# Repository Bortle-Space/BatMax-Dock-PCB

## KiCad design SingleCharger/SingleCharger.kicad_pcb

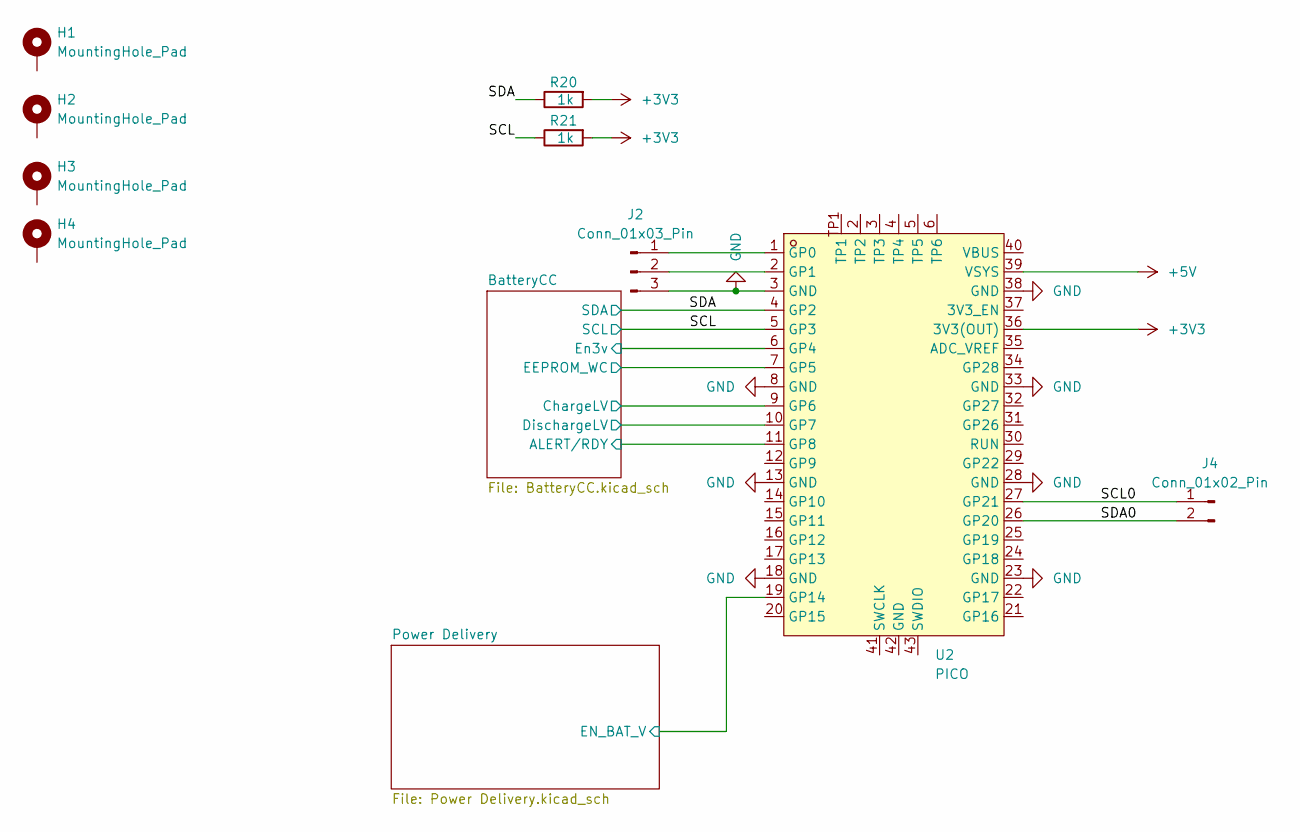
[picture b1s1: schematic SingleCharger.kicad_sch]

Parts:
H1, H2, H3, H4: MountingHole_Pad; MountingHole_3.2mm_M3_DIN965_Pad_TopBottom
J2: Conn_01x03_Pin; PinHeader_1x03_P2.54mm_Vertical
J4: Conn_01x02_Pin; PinHeader_1x02_P2.54mm_Vertical
R20, R21: 1k; R_1206_3216Metric_Pad1.30x1.75mm_HandSolder
U2: PICO; RaspberryPi_Pico_Common_THT; LCSC Part C7203002

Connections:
+3V3: R20.2, R21.2, U2.36 (3V3(OUT)); also elsewhere on the board
+5V: U2.39 (VSYS); also elsewhere on the board
/BatteryCC/ALERT/RDY: U2.11 (GP8); also elsewhere on the board
/BatteryCC/Battery/EEPROM_WC: U2.7 (GP5); also elsewhere on the board
/BatteryCC/ChargeLV: U2.9 (GP6); also elsewhere on the board
/DischargeLV: U2.10 (GP7)
/En3v: U2.6 (GP4)
/Power Delivery/EN_BAT_V: U2.19 (GP14); also elsewhere on the board
/SCL: R21.1, U2.5 (GP3); also elsewhere on the board
/SCL0: J4.1, U2.27 (GP21)
/SDA: R20.1, U2.4 (GP2); also elsewhere on the board
/SDA0: J4.2, U2.26 (GP20)
GND: J2.3, U2.3 (GND), U2.8 (GND), U2.13 (GND), U2.18 (GND), U2.23 (GND), U2.28 (GND), U2.33 (GND), U2.38 (GND); also elsewhere on the board
unnamed: J2.1, U2.1 (GP0)
unnamed: J2.2, U2.2 (GP1)

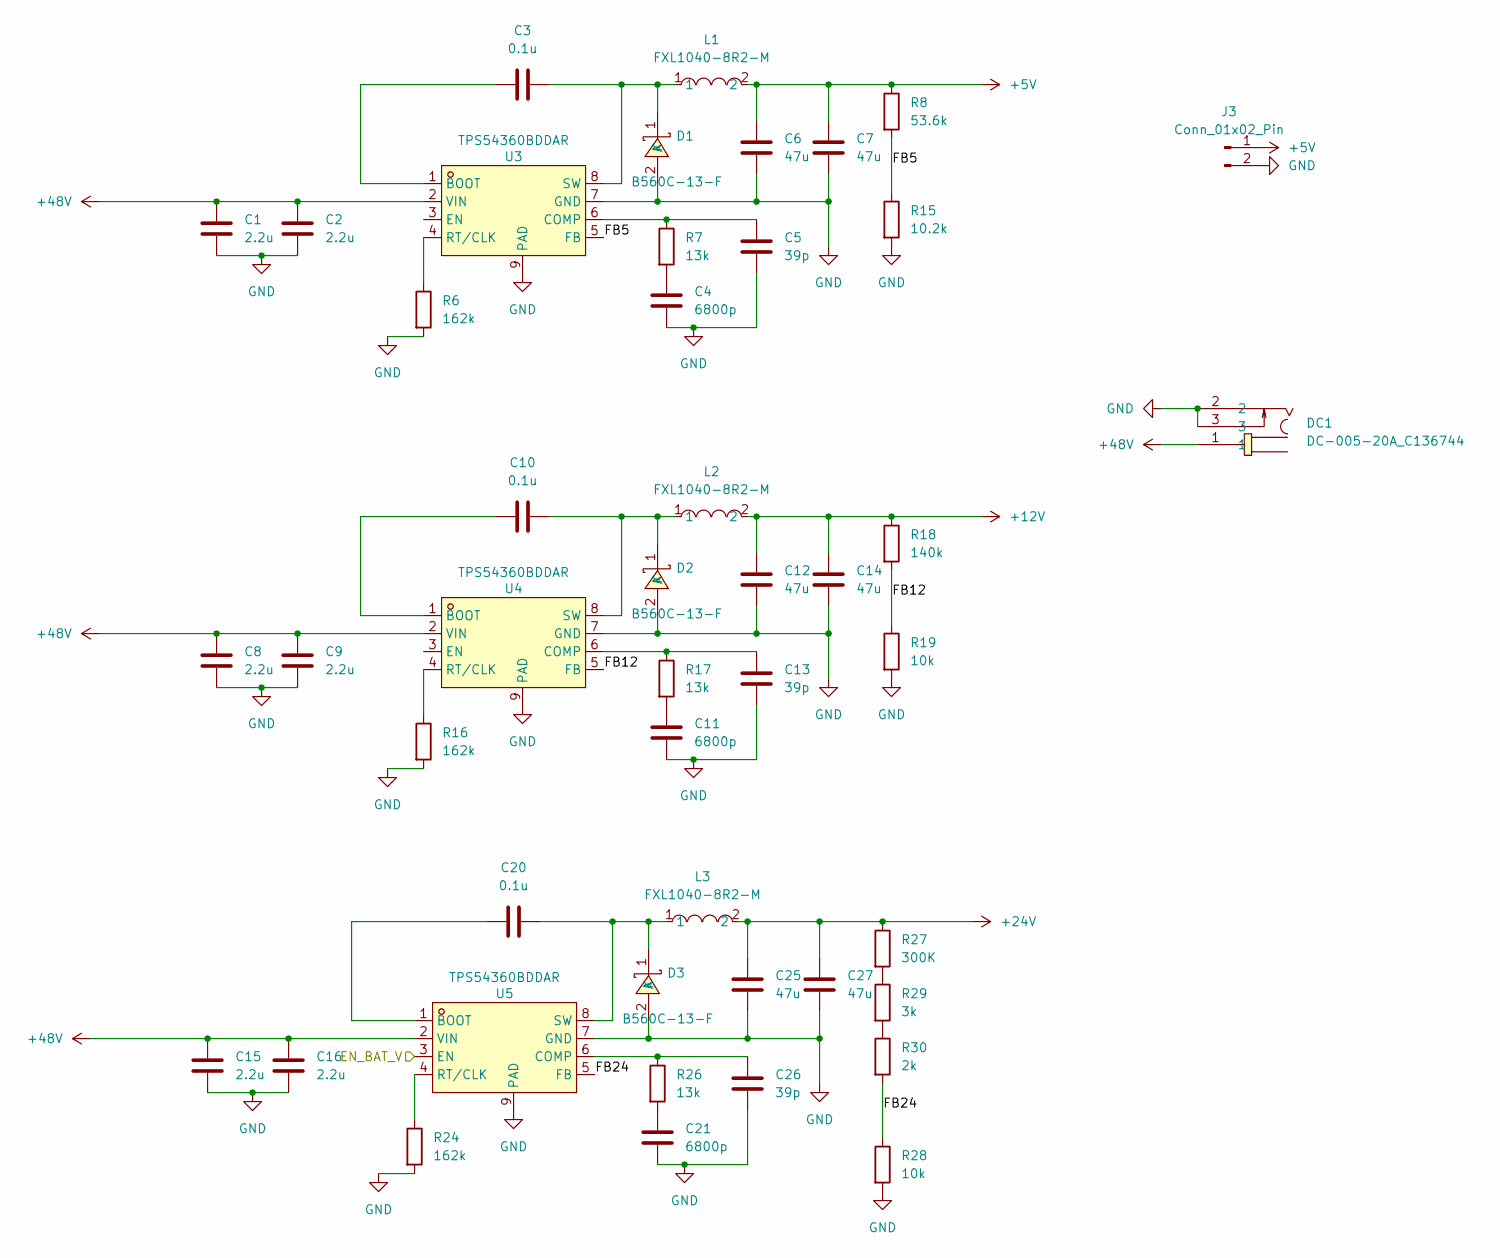
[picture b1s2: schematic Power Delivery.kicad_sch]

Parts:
C1, C2, C8, C9, C15, C16: 2.2u; C_1206_3216Metric; LCSC Part C170101
C3, C10, C20: 0.1u; C_1206_3216Metric; LCSC Part C56392
C4, C11, C21: 6800p; C_1206_3216Metric; LCSC Part C2760541
C5, C13, C26: 39p; C_1206_3216Metric; LCSC Part C5186878
C6, C7, C12, C14, C25, C27: 47u; C_1206_3216Metric; LCSC Part C94034
D1, D2, D3: B560C-13-F; SMC_L7.1-W6.2-LS8.1-RD; LCSC Part C85100
DC1: DC-005-20A_C136744; DC-IN-TH_DC-005-20A; LCSC Part C136744
J3: Conn_01x02_Pin; PinHeader_1x02_P2.54mm_Vertical
L1, L2, L3: FXL1040-8R2-M; IND-SMD_L11.5-W10.0_FXL1040; LCSC Part C167232
R6, R16, R24: 162k; R_1206_3216Metric_Pad1.30x1.75mm_HandSolder; LCSC Part C22815
R7, R17, R26: 13k; R_1206_3216Metric_Pad1.30x1.75mm_HandSolder; LCSC Part C445658
R8: 53.6k; R_1206_3216Metric_Pad1.30x1.75mm_HandSolder; LCSC Part C21398
R15: 10.2k; R_1206_3216Metric_Pad1.30x1.75mm_HandSolder; LCSC Part C21398
R18: 140k; R_1206_3216Metric_Pad1.30x1.75mm_HandSolder; LCSC Part C21398
R19, R28: 10k; R_1206_3216Metric_Pad1.30x1.75mm_HandSolder; LCSC Part C21398
R27: 300K; R_1206_3216Metric_Pad1.30x1.75mm_HandSolder; LCSC Part C21398
R29: 3k; R_1206_3216Metric_Pad1.30x1.75mm_HandSolder; LCSC Part C21398
R30: 2k; R_1206_3216Metric_Pad1.30x1.75mm_HandSolder; LCSC Part C21398
U3, U4, U5: TPS54360BDDAR; SOIC-8_L5.0-W4.0-P1.27-LS6.0-BL-EP2.0; LCSC Part C524806

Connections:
+5V: C6.1, C7.1, J3.1, L1.2, R8.1; also elsewhere on the board
+12V: C12.1, C14.1, L2.2, R18.1; also elsewhere on the board
+24V: C25.1, C27.1, L3.2, R27.1; also elsewhere on the board
+48V: C1.1, C2.1, C8.1, C9.1, C15.1, C16.1, DC1.1, U3.2 (VIN), U4.2 (VIN), U5.2 (VIN)
/Power Delivery/EN_BAT_V: U5.3 (EN); also elsewhere on the board
/Power Delivery/FB5: R8.2, R15.1, U3.5 (FB)
/Power Delivery/FB12: R18.2, R19.1, U4.5 (FB)
/Power Delivery/FB24: R28.1, R30.2, U5.5 (FB)
GND: C1.2, C2.2, C4.2, C5.2, C6.2, C7.2, C8.2, C9.2, C11.2, C12.2, C13.2, C14.2, C15.2, C16.2, C21.2, C25.2, C26.2, C27.2, D1.2 (A), D2.2 (A), D3.2 (A), DC1.2, DC1.3, J3.2, R6.2, R15.2, R16.2, R19.2, R24.2, R28.2, U3.7 (GND), U3.9 (PAD), U4.7 (GND), U4.9 (PAD), U5.7 (GND), U5.9 (PAD); also elsewhere on the board
unnamed: C4.1, R7.2
unnamed: C11.1, R17.2
unnamed: C21.1, R26.2
unnamed: C3.2, D1.1 (K), L1.1, U3.8 (SW)
unnamed: C10.2, D2.1 (K), L2.1, U4.8 (SW)
unnamed: C20.2, D3.1 (K), L3.1, U5.8 (SW)
unnamed: R27.2, R29.1
unnamed: R29.2, R30.1
unnamed: C3.1, U3.1 (BOOT)
unnamed: C5.1, R7.1, U3.6 (COMP)
unnamed: R6.1, U3.4 (RT/CLK)
unnamed: C10.1, U4.1 (BOOT)
unnamed: C13.1, R17.1, U4.6 (COMP)
unnamed: R16.1, U4.4 (RT/CLK)
unnamed: C20.1, U5.1 (BOOT)
unnamed: C26.1, R26.1, U5.6 (COMP)
unnamed: R24.1, U5.4 (RT/CLK)

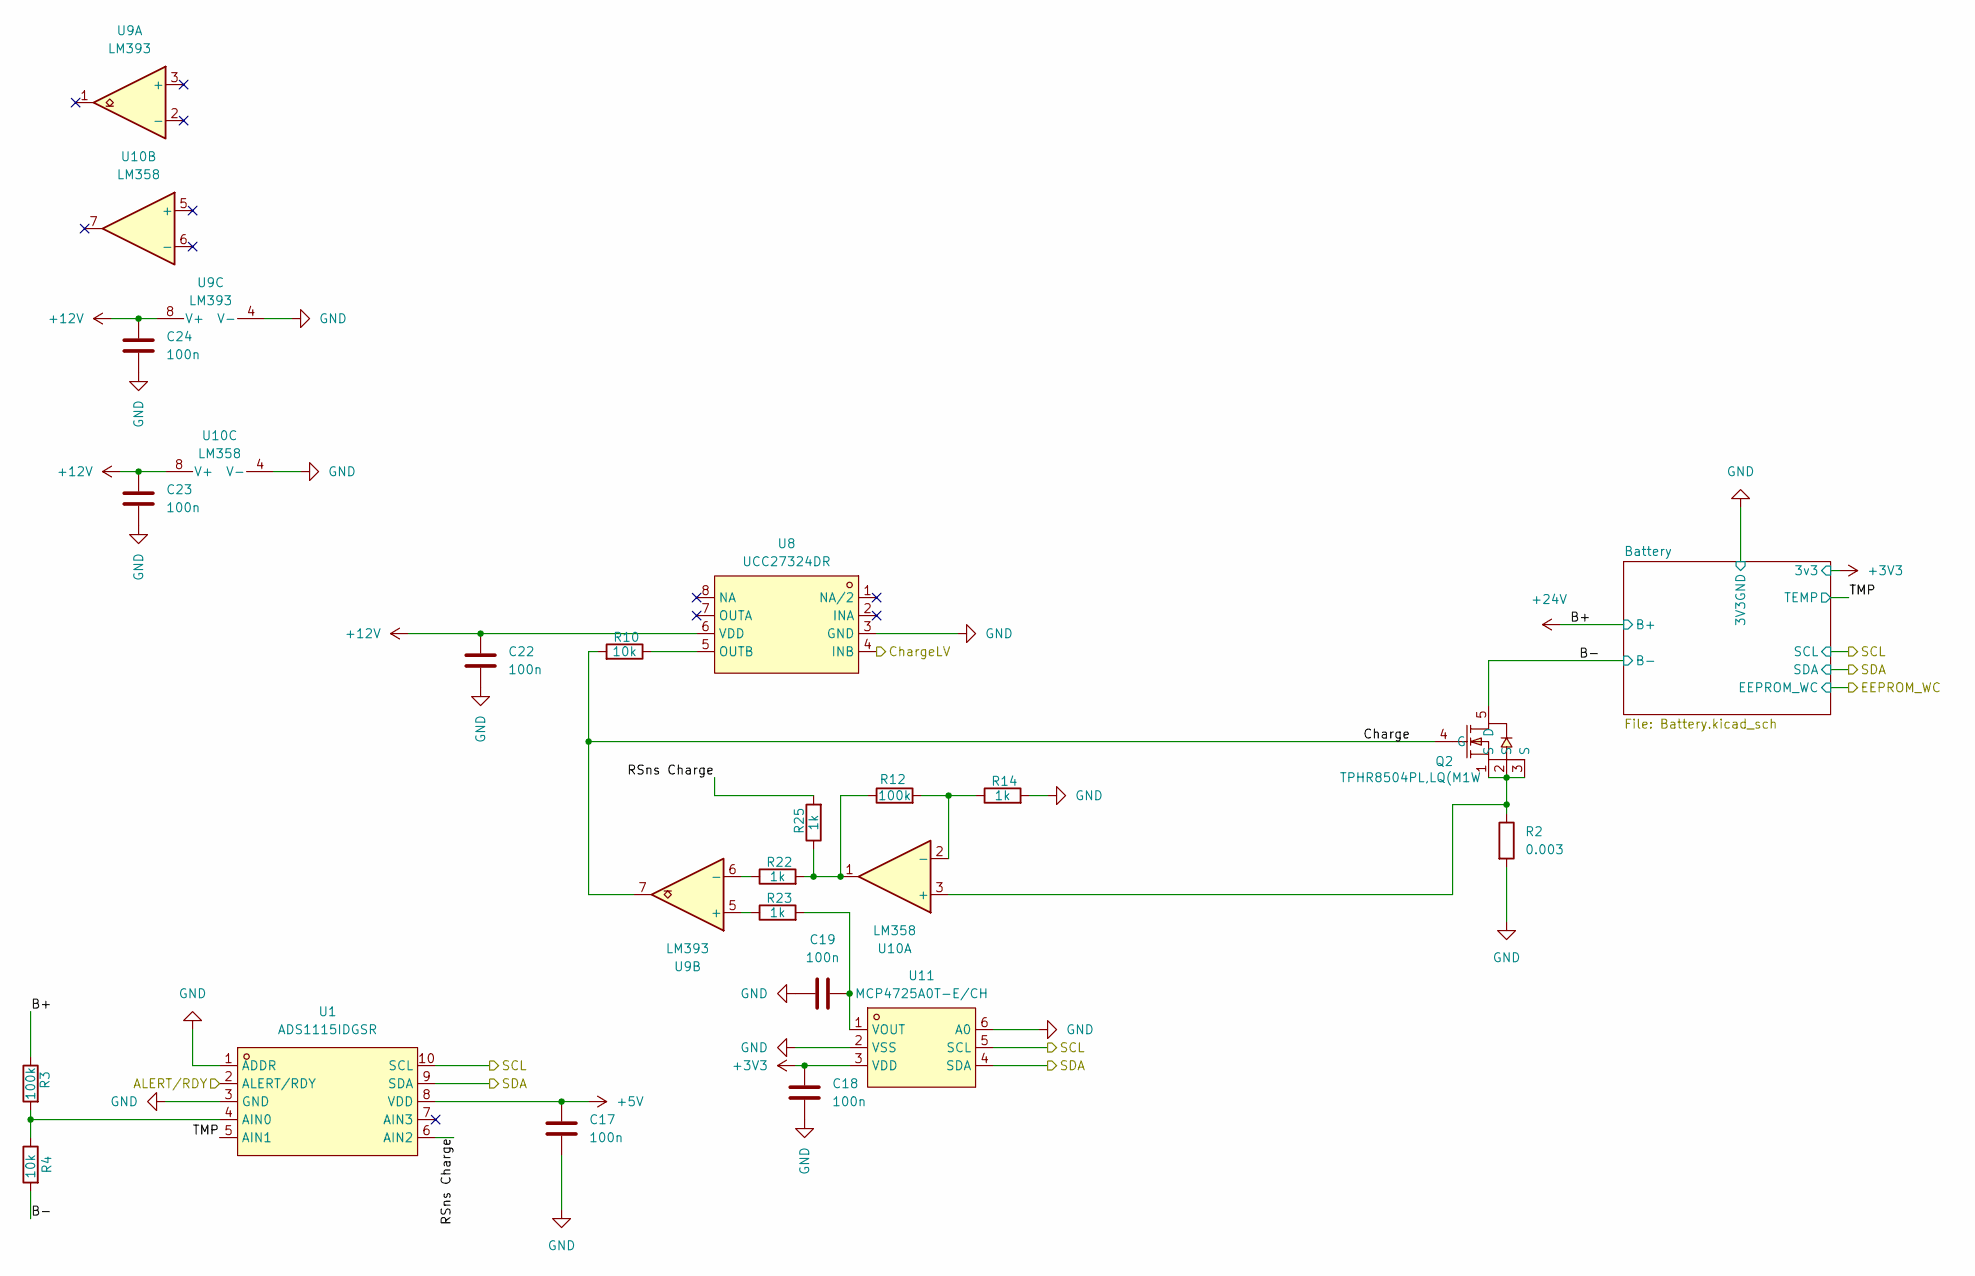
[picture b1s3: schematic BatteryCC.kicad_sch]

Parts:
C17, C18, C19, C22, C23, C24: 100n; R_1206_3216Metric_Pad1.30x1.75mm_HandSolder
Q2: TPHR8504PL,LQ(M1W; DFN-5_L4.9-W5.9-P1.27-LS6.2-BL; LCSC Part C22388172
R2: 0.003; R_1206_3216Metric_Pad1.30x1.75mm_HandSolder
R3, R12: 100k; R_1206_3216Metric_Pad1.30x1.75mm_HandSolder
R4, R10: 10k; R_1206_3216Metric_Pad1.30x1.75mm_HandSolder
R14, R22, R23, R25: 1k; R_1206_3216Metric_Pad1.30x1.75mm_HandSolder
U1: ADS1115IDGSR; MSOP-10_L3.0-W3.0-P0.50-LS5.0-BL; LCSC Part C37593
U8: UCC27324DR; SOIC-8_L5.0-W4.0-P1.27-LS6.0-BL; LCSC Part C46427
U9: LM393; SOP-8_L4.9-W3.9-P1.27-LS6.0-BL
U10: LM358; SOP-8_L4.9-W3.9-P1.27-LS6.0-BL
U11: MCP4725A0T-E/CH; SOT-23-6_L2.9-W1.6-P0.95-LS2.8-BL; LCSC Part C144198

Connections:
+3V3: C18.1, U11.3 (VDD); also elsewhere on the board
+5V: C17.1, U1.8 (VDD); also elsewhere on the board
+12V: C22.1, C23.1, C24.1, U8.6 (VDD), U9.8 (V+), U10.8 (V+); also elsewhere on the board
+24V: R3.1; also elsewhere on the board
/BatteryCC/ALERT/RDY: U1.2 (ALERT/RDY); also elsewhere on the board
/BatteryCC/B-: Q2.5 (D), R4.2; also elsewhere on the board
/BatteryCC/Charge: Q2.4 (G), R10.2, U9.7
/BatteryCC/ChargeLV: U8.4 (INB); also elsewhere on the board
/BatteryCC/RSns Charge: R25.2, U1.6 (AIN2)
/BatteryCC/TMP: U1.5 (AIN1); also elsewhere on the board
/SCL: U1.10 (SCL), U11.5 (SCL); also elsewhere on the board
/SDA: U1.9 (SDA), U11.4 (SDA); also elsewhere on the board
GND: C17.2, C18.2, C19.1, C22.2, C23.2, C24.2, R2.2, R14.2, U1.1 (ADDR), U1.3 (GND), U8.3 (GND), U9.4 (V-), U10.4 (V-), U11.2 (VSS), U11.6 (A0); also elsewhere on the board
unnamed: R12.1, R22.2, R25.1, U10.1
unnamed: R3.2, R4.1, U1.4 (AIN0)
unnamed: R10.1, U8.5 (OUTB)
unnamed: R23.1, U9.5 (+)
unnamed: R22.1, U9.6 (-)
unnamed: Q2.1 (S), Q2.2 (S), Q2.3 (S), R2.1, U10.3 (+)
unnamed: R12.2, R14.1, U10.2 (-)
unnamed: C19.2, R23.2, U11.1 (VOUT)

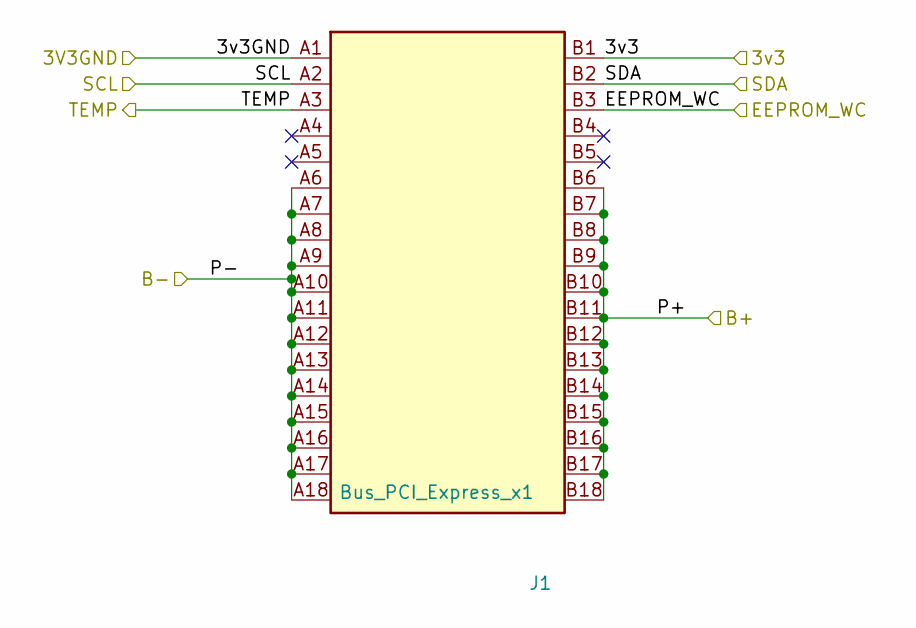
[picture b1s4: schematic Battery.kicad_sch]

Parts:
J1: Bus_PCI_Express_x1; CONN-TH_36P-P1.00-V_3183-XXXXXPXT

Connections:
+3V3: J1.B1; also elsewhere on the board
+24V: J1.B6, J1.B7, J1.B8, J1.B9, J1.B10, J1.B11, J1.B12, J1.B13, J1.B14, J1.B15, J1.B16, J1.B17, J1.B18; also elsewhere on the board
/BatteryCC/B-: J1.A6, J1.A7, J1.A8, J1.A9, J1.A10, J1.A11, J1.A12, J1.A13, J1.A14, J1.A15, J1.A16, J1.A17, J1.A18; also elsewhere on the board
/BatteryCC/Battery/EEPROM_WC: J1.B3; also elsewhere on the board
/BatteryCC/TMP: J1.A3; also elsewhere on the board
/SCL: J1.A2; also elsewhere on the board
/SDA: J1.B2; also elsewhere on the board
GND: J1.A1; also elsewhere on the board

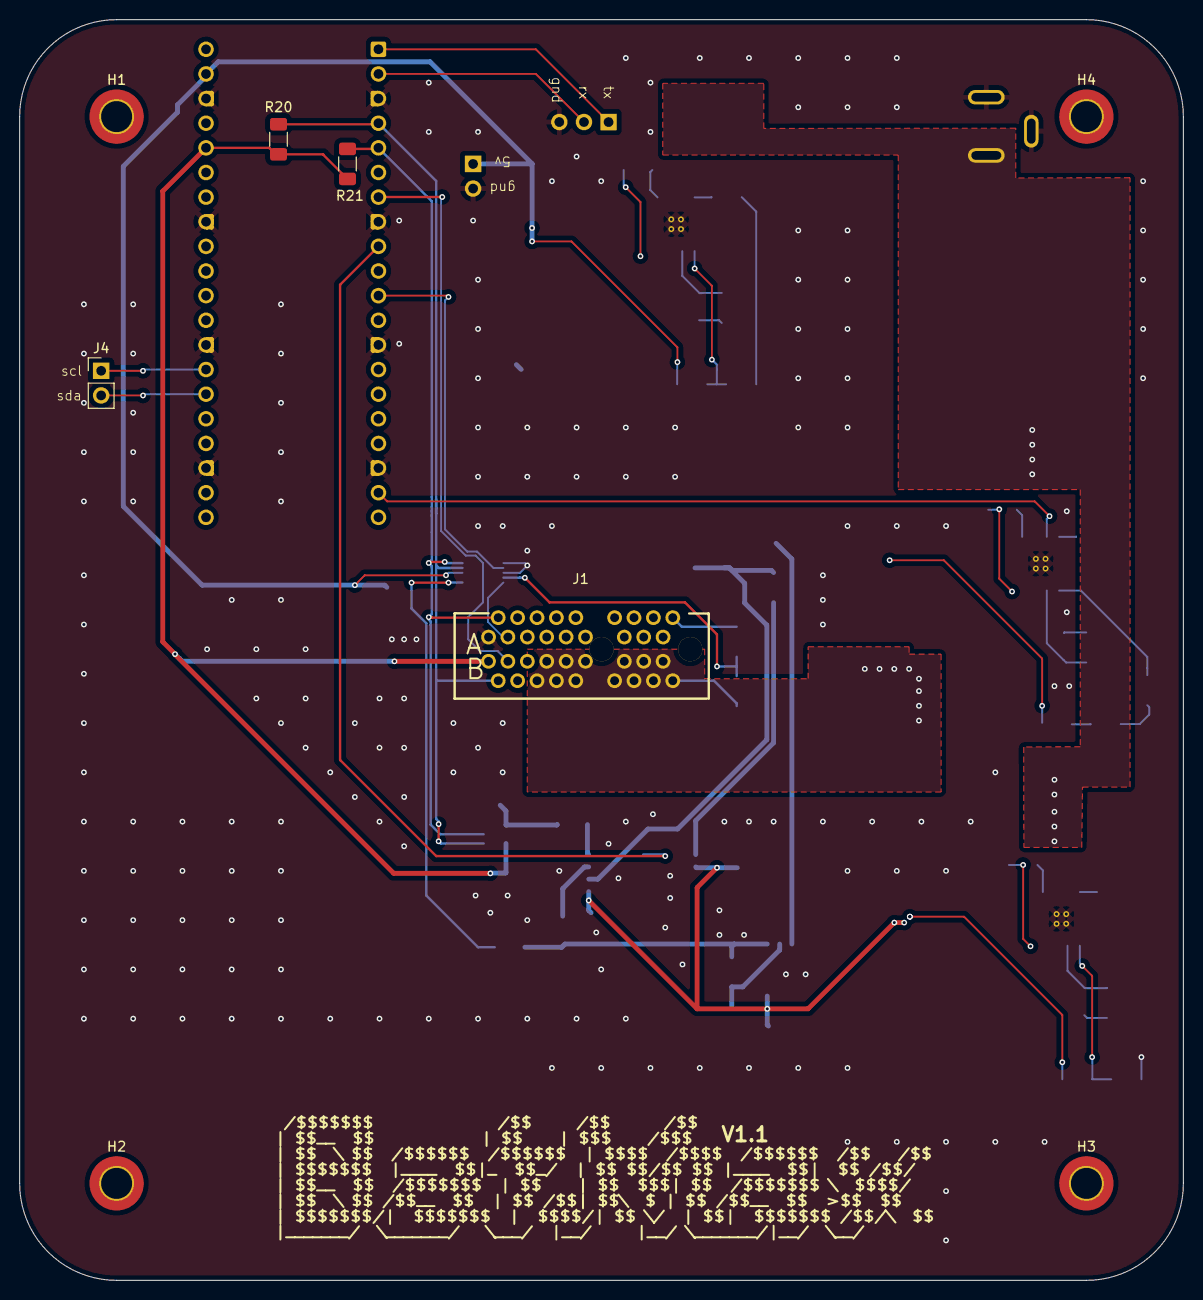
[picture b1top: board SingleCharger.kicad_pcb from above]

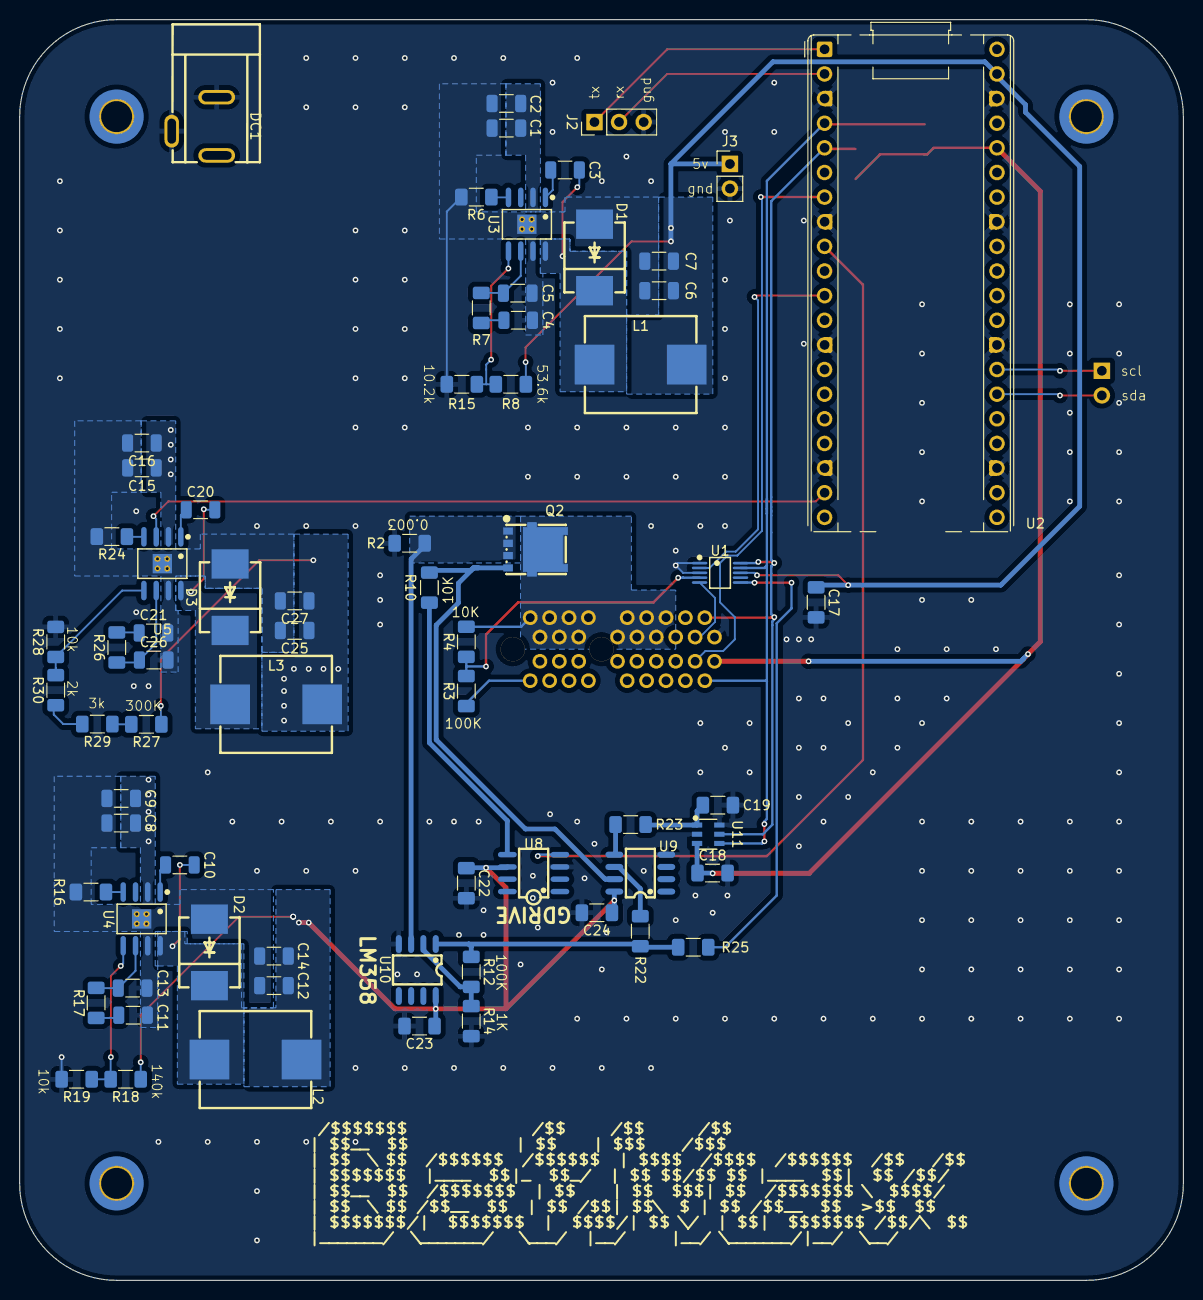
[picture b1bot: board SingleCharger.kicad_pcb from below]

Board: 2 copper layers, 120.0 x 130.0 mm, 77 parts (69 on the bottom side), 48 nets.

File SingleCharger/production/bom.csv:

Designator,Footprint,Quantity,Value,LCSC Part #
"C1, C15, C16, C2, C8, C9",1206,6,2.2u,C170101
"C10, C20, C3",1206,3,0.1u,C56392
"C11, C21, C4",1206,3,6800p,C2760541
"C12, C14, C25, C27, C6, C7",1206,6,47u,C94034
"C13, C26, C5",1206,3,39p,C5186878
"C17, C18, C19, C22, C23, C24",1206,6,100n,
"D1, D2, D3",SMC_L7.1-W6.2-LS8.1-RD,3,B560C-13-F,C85100
DC1,DC-IN-TH_DC-005-20A,1,DC-005-20A_C136744,C136744
J1,CONN-TH_36P-P1.00-V_3183-XXXXXPXT,1,Bus_PCI_Express_x1,
J2,PinHeader_1x03_P2.54mm_Vertical,1,Conn_01x03_Pin,
"J3, J4",PinHeader_1x02_P2.54mm_Vertical,2,Conn_01x02_Pin,
"L1, L2, L3",IND-SMD_L11.5-W10.0_FXL1040,3,FXL1040-8R2-M,C167232
Q2,DFN-5_L4.9-W5.9-P1.27-LS6.2-BL,1,"TPHR8504PL,LQ(M1W",C22388172
"R10, R4",1206,2,10k,
"R12, R3",1206,2,100k,
"R14, R20, R21, R22, R23, R25",1206,6,1k,
R15,1206,1,10.2k,C21398
"R16, R24, R6",1206,3,162k,C22815
"R17, R26, R7",1206,3,13k,C445658
R18,1206,1,140k,C21398
"R19, R28",1206,2,10k,C21398
R2,1206,1,0.003,
R27,1206,1,300K,C21398
R29,1206,1,3k,C21398
R30,1206,1,2k,C21398
R8,1206,1,53.6k,C21398
U1,MSOP-10_L3.0-W3.0-P0.50-LS5.0-BL,1,ADS1115IDGSR,C37593
U10,SOP-8_L4.9-W3.9-P1.27-LS6.0-BL,1,LM358,
U11,SOT-23-6_L2.9-W1.6-P0.95-LS2.8-BL,1,MCP4725A0T-E/CH,C144198
U2,RaspberryPi_Pico_Common_THT,1,PICO,C7203002
"U3, U4, U5",SOIC-8_L5.0-W4.0-P1.27-LS6.0-BL-EP2.0,3,TPS54360BDDAR,C524806
U8,SOIC-8_L5.0-W4.0-P1.27-LS6.0-BL,1,UCC27324DR,C46427
U9,SOP-8_L4.9-W3.9-P1.27-LS6.0-BL,1,LM393,

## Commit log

2025-03-17 First push
2025-03-17 wORKING ON REFACTOR
2025-03-18 Added.
2025-03-18 Rebuild
2025-03-18 Working.
2025-03-18 Almost done with layout.
2025-03-18 Finished layout and routing.
2025-03-24 Fixed some 3D Models.
2025-03-24 Moved to +48V Feed. 25.2 Controlled by Pico.
2025-03-24 Updated Production Files.
2025-03-24 Updated Version, and Production Files.
2025-03-24 Added SCL/SDA Pins.
2025-03-28 Moved some things around.
